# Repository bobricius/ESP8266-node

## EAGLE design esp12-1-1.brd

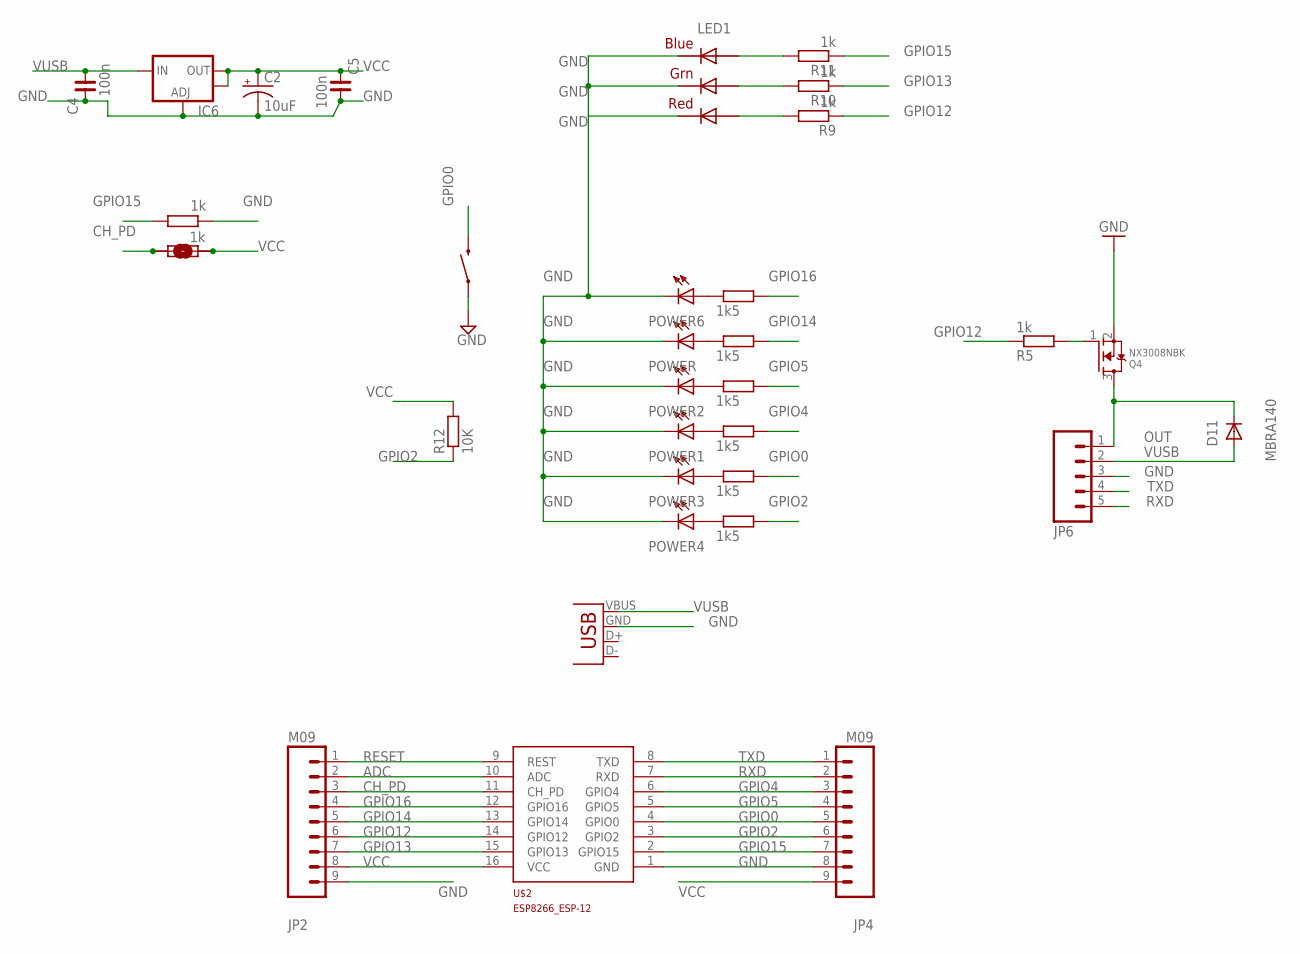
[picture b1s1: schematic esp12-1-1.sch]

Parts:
C2: 10uF; EIA3216
C4, C5: 100n; C0603
D11: MBRA140; SOD-323
IC6: V_REG_LM1117SOT223; SOT223
JP2, JP4: M09; 1X09
JP6: M05NO_SILK; 1X05_NO_SILK
LED1: RGBLED5050
POWER, POWER1, POWER2, POWER3, POWER4, POWER6: NA; LED-0603
PWR2: SOLDERJUMPERNO; SJ_2S-NO
Q4: NX3008NBK; SOT23-WIDE
R1, R2, R3, R4, R6, R13: 1k5; R0603
R5, R7, R8, R9, R10, R11: 1k; R0603
R12: 10K; R0603
RESET1: SWITCH-MOMENTARY-2-SMD-1101NE; TACTILE-SWITCH-1101NE
U$2: ESP8266_ESP-12; ESP8266-ESP12
X3: USB-A-H

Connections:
ADC: JP2.2, U$2.10 (ADC)
CH_PD: JP2.3, PWR2.1, R8.2, U$2.11 (CH_PD)
GND: C2.C (-), C4.2, C5.1, IC6.1 (ADJ), JP2.9, JP4.8, JP6.3, LED1.4 (BLUE_C), LED1.5 (RED_C), LED1.6 (GREEN_C), POWER.C, POWER1.C, POWER2.C, POWER3.C, POWER4.C, POWER6.C, Q4.2 (S), R7.2, RESET1.P$1 (1), U$2.1 (GND), X3.GND (VBUS)
GPIO0: JP4.5, R3.2, RESET1.P$2 (2), U$2.4 (GPIO0)
GPIO2: JP4.6, R4.2, R12.1, U$2.3 (GPIO2)
GPIO4: JP4.3, R1.2, U$2.6 (GPIO4)
GPIO5: JP4.4, R2.2, U$2.5 (GPIO5)
GPIO12: JP2.6, R5.1, R9.1, U$2.14 (GPIO12)
GPIO13: JP2.7, R10.1, U$2.15 (GPIO13)
GPIO13X: LED1.2 (RED_A), R9.2
GPIO14: JP2.5, R13.2, U$2.13 (GPIO14)
GPIO15: JP4.7, R7.1, R11.1, U$2.2 (GPIO15)
GPIO16: JP2.4, R6.2, U$2.12 (GPIO16)
unnamed: POWER1.A, R1.1
unnamed: POWER2.A, R2.1
unnamed: POWER3.A, R3.1
unnamed: POWER4.A, R4.1
unnamed: Q4.1 (G), R5.2
unnamed: POWER6.A, R6.1
unnamed: LED1.3 (BLUE_A), R11.2
unnamed: LED1.1 (GREEN_A), R10.2
unnamed: POWER.A, R13.1
OUT: D11.1 (C), JP6.1, Q4.3 (D)
RESET: JP2.1, U$2.9 (REST)
RXD: JP4.2, JP6.5, U$2.7 (RXD)
TXD: JP4.1, JP6.4, U$2.8 (TXD)
VCC: C2.A (+), C5.2, IC6.2 (OUT), IC6.4 (OUT), JP2.8, JP4.9, PWR2.2, R8.1, R12.2, U$2.16 (VCC)
VUSB: C4.1, D11.2 (A), IC6.3 (IN), JP6.2, X3.VBUS (GND)

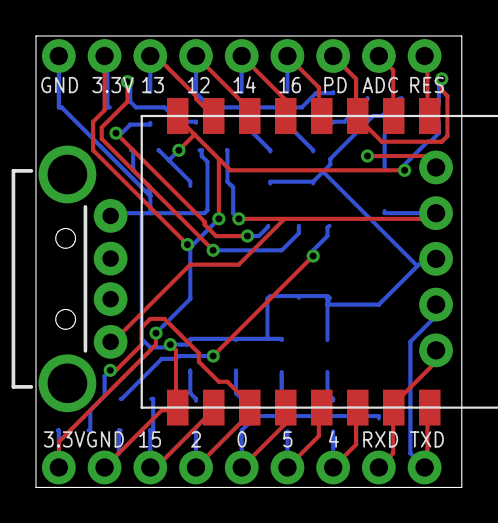
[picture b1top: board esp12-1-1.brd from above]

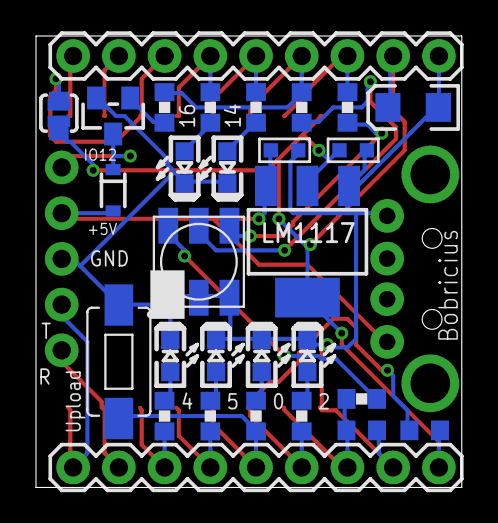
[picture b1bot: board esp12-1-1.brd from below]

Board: 2 copper layers, 23.7 x 25.1 mm, 33 parts (30 on the bottom side), 28 nets.

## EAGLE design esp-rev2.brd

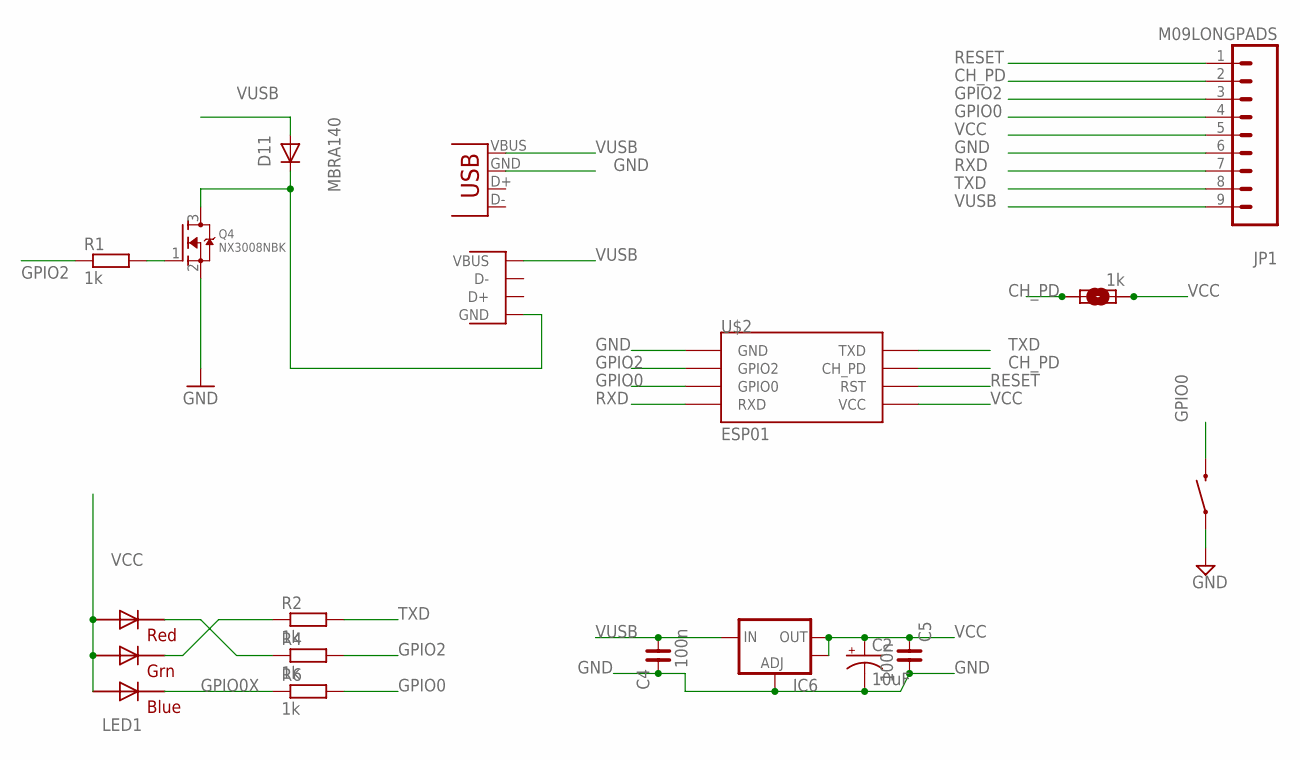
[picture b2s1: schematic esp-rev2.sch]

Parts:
C2: 10uF; EIA3216
C4, C5: 100n; C0603
D11: MBRA140; SOD-323
IC6: V_REG_LM1117SOT223; SOT223
JP1: M09LONGPADS; 1X09_LONGPADS
LED1: RGBLED5050
PWR2: SOLDERJUMPERTRACE; SJ_2S-TRACE
Q4: NX3008NBK; SOT23-WIDE
R1, R2, R4, R6, R8: 1k; R0603
RESET1: SWITCH-MOMENTARY-2-SMD-1101NE; TACTILE-SWITCH-1101NE
U$2: ESP01
X1, X3: USB-A-H

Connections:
CH_PD: JP1.2, PWR2.1, R8.2, U$2.CH_PD
GND: C2.C (-), C4.2, C5.1, IC6.1 (ADJ), JP1.6, Q4.2 (S), RESET1.P$1 (1), U$2.GND, X3.GND (VBUS)
GPIO0: JP1.4, R6.2, RESET1.P$2 (2), U$2.GPIO0
GPIO0X: LED1.4 (BLUE_C), R6.1
GPIO2: JP1.3, R1.1, R4.2, U$2.GPIO2
unnamed: LED1.5 (RED_C), R4.1
unnamed: LED1.6 (GREEN_C), R2.1
unnamed: Q4.1 (G), R1.2
unnamed: D11.1 (C), Q4.3 (D), X1.GND
RESET: JP1.1, U$2.RST
RXD: JP1.7, U$2.RX (RXD)
TXD: JP1.8, R2.2, U$2.TX (TXD)
VCC: C2.A (+), C5.2, IC6.2 (OUT), IC6.4 (OUT), JP1.5, LED1.1 (GREEN_A), LED1.2 (RED_A), LED1.3 (BLUE_A), PWR2.2, R8.1, U$2.VCC
VUSB: C4.1, D11.2 (A), IC6.3 (IN), JP1.9, X1.VBUS, X3.VBUS (GND)

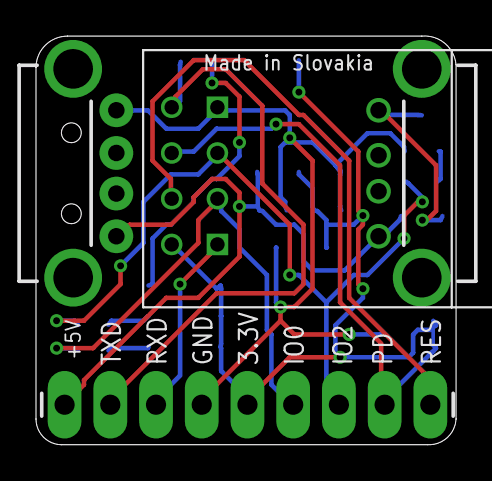
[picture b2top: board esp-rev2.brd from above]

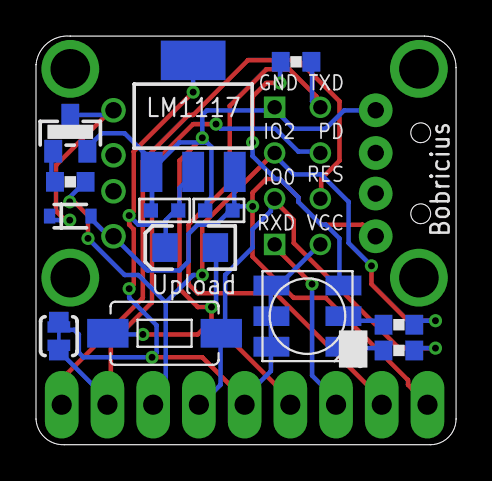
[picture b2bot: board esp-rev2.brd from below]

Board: 2 copper layers, 23.3 x 22.7 mm, 18 parts (14 on the bottom side), 14 nets.

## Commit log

2015-05-07 :circus_tent: Added .gitattributes & .gitignore files
2015-05-07 Firtst upload

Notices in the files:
parts and their libraries:
SparkFun-Connectors: Licensing: Creative Commons ShareAlike 4.0 International - https://creativecommons.org/licenses/by-sa/4.0
microbuilder: This work is placed in the public domain, and may be freely used for commercial and non-commercial work with the following conditions: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
